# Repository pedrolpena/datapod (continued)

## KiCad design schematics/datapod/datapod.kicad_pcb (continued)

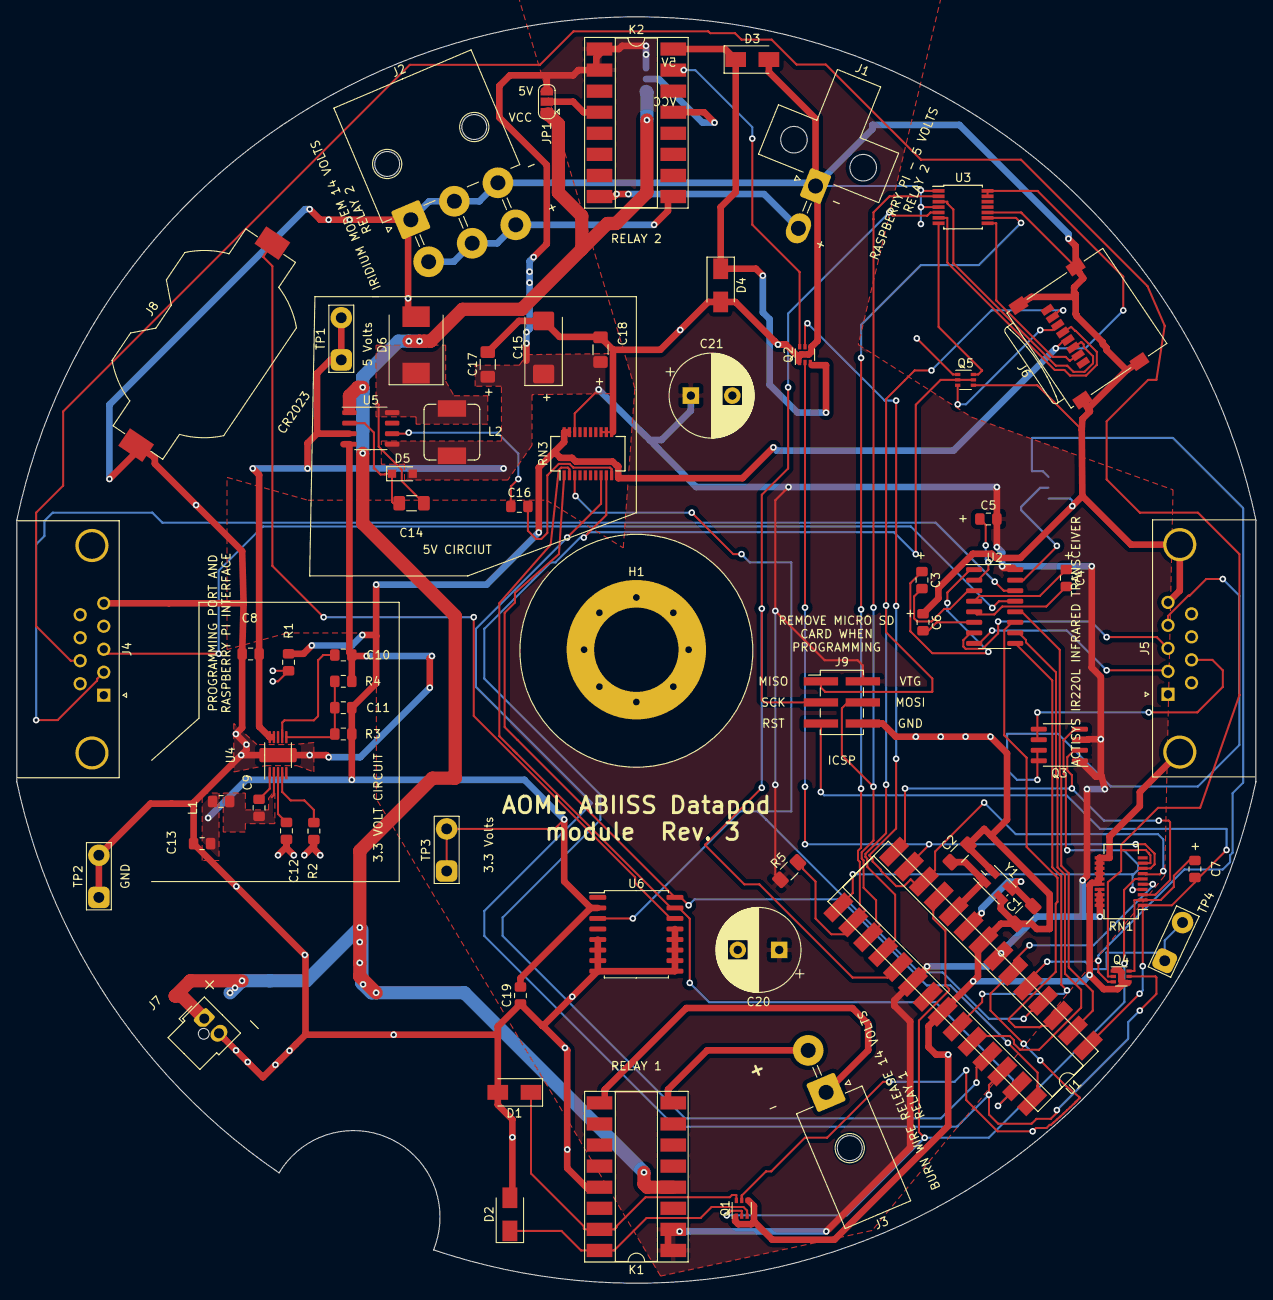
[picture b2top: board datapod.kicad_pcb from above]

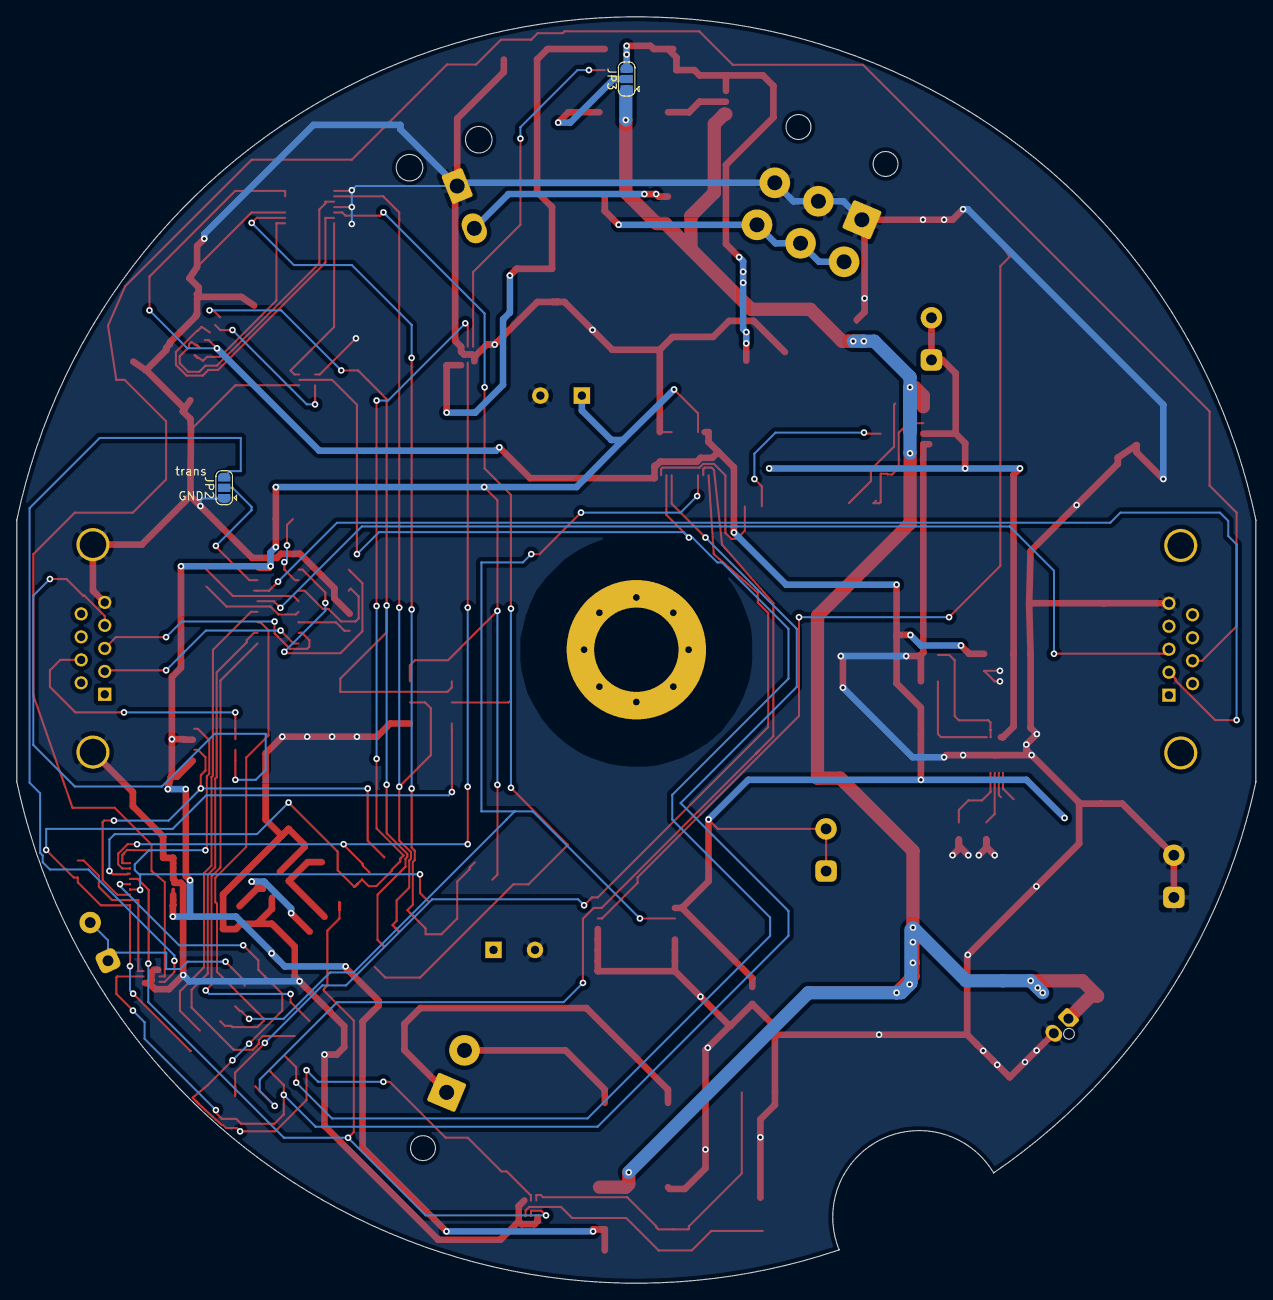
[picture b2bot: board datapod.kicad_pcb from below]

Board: 2 copper layers, 149.3 x 152.6 mm, 67 parts (2 on the bottom side), 69 nets.

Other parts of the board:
JP3: Jumper_3_Open; SolderJumper-3_P1.3mm_Open_RoundedPad1.0x1.5mm

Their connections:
+5V: JP3.3; also elsewhere on the board

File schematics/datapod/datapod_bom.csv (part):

Reference, Value, Vendor, Part#, Footprint, Datasheet,, extra, part#,, Datasheet2, Value2, Part#-2, Field4, Field5, Field6, Field7, Field8
Y1,16Mhz,Digikey,SER3686DKR-ND,Oscillator:Oscillator_SMD_EuroQuartz_XO32-4Pin_3.2x2.5mm_HandSoldering,https://support.epson.biz/td/api/doc_check.php?dl=brief_FA-2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,,https://www.digikey.com/product-detail/en/epson/FA-238-16.00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,,,,,,,,,,
C1,22pF,Digikey,399-8165-1-ND,Capacitor_SMD:C_1206_3216Metric_Pad1.42x1.75mm_HandSolder,https://api.kemet.com/component-edge/download/datasheet/C120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,,,,,,,,,,,,
RN1,R_Pack 10k Ohms,Digikey,OSOPT-10KACT-ND ,Package_SO:SSOP-20_3.9x8.7mm_P0.635mm,http://www.vishay.com/docs/60002/osop.pdf,,,,,,,,,,,,
C2,22pF,Digikey,399-8165-1-ND,Capacitor_SMD:C_1206_3216Metric_Pad1.42x1.75mm_HandSolder,https://api.kemet.com/component-edge/download/datasheet/C120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,,,,,,,,,,,,
H1,MountingHole,,N/A,datapod:MountingHole_0.4_inches_Pad_Via,~,,,,,,,,,,,,
U1,ATmega328P-PU,  ,N/A,Package_DIP:DIP-28_W7.62mm_SMDSocket_SmallPads,http://ww1.microchip.com/downloads/en/DeviceDoc/ATmega328_P%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,,,,,https://www.digikey.com/products/en?mpart=110-47-328-41-105000&v=54,110-47-328-41-105000 ,,,,,,
J9,Conn_02x03_Odd_Even,Digikey,1175-1864-ND,Connector_PinHeader_2.54mm:PinHeader_2x03_P2.54mm_Vertical_SMD,http://www.cnctech.us/pdfs/3020-XX-0300-00-TR.pdf,,,,,,,,,,,,
TP2,TestPoint_2Pole,,N/A,TestPoint:TestPoint_2Pads_Pitch5.08mm_Drill1.3mm,~,,,,,,,,,,,,
TP4,TestPoint_2Pole,,N/A,TestPoint:TestPoint_2Pads_Pitch5.08mm_Drill1.3mm,~,,,,,,,,,,,,
Q1,FDG1024NZ,Digikey,FDG1024NZFSCT-ND,Package_TO_SOT_SMD:SOT-363_SC-70-6,http://www.fairchildsemi.com/ds/FD/FDG1024NZ.pdf,,,,,,,,,,,,
D1,B220A-13-F ,Digikey,B220A-FDIDKR-ND,Diode_SMD:D_SMA,http://www.jameco.com/Jameco/Products/ProdDS/1538777.pdf,,,,,,,,,,,,
D2,B220A-13-F ,Digikey,B220A-FDIDKR-ND,Diode_SMD:D_SMA,http://www.jameco.com/Jameco/Products/ProdDS/1538777.pdf,,,,,,,,,,,,
Q2,FDG1024NZ,Digikey,FDG1024NZFSCT-ND,Package_TO_SOT_SMD:SOT-363_SC-70-6,http://www.fairchildsemi.com/ds/FD/FDG1024NZ.pdf,,,,,,,,,,,,
D3,B220A-13-F ,Digikey,B220A-FDIDKR-ND,Diode_SMD:D_SMA,http://www.jameco.com/Jameco/Products/ProdDS/1538777.pdf,,,,,,,,,,,,
D4,B220A-13-F ,Digikey,B220A-FDIDKR-ND,Diode_SMD:D_SMA,http://www.jameco.com/Jameco/Products/ProdDS/1538777.pdf,,,,,,,,,,,,
K1,DS2E-SL2-DC5V,Digikey,ED11086-ND,Package_DIP:DIP-16_W7.62mm_SMDSocket_SmallPads,https://www3.panasonic.biz/ac/e_download/control/relay/signa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,,,,,,,255-1066-ND,,,,,
J3,Conn_01x02,Digikey,WM11969-ND,Connector_Molex:Molex_Mega-Fit_76825-0002_2x01_P5.70mm_Horizontal,https://media.digikey.com/pdf/Data%20Sheets/Molex%20PDFs/Meg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,,,,,,,,,,,,
J2,Conn_02x03_Odd_Even,Digikey,WM11971-ND,Connector_Molex:Molex_Mega-Fit_76825-0006_2x03_P5.70mm_Horizontal,https://www.molex.com/pdm_docs/as/AS-76823-100.pdf,,,,,,,,,,,,
J1,Conn_01x02,Digikey,WM3900-ND,Connector_Molex:Molex_Mini-Fit_Jr_5569-02A1_2x01_P4.20mm_Horizontal,https://www.molex.com/pdm_docs/sd/039291028_sd.pdf,,,,,,,,,,,,
K2,DS2E-SL2-DC5V,Digikey,ED11086-ND,Package_DIP:DIP-16_W7.62mm_SMDSocket_SmallPads,https://www3.panasonic.biz/ac/e_download/control/relay/signa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,,,,,,,255-1066-ND,,,,,
JP1,Jumper_3_Open,,N/A,Jumper:SolderJumper-3_P1.3mm_Open_RoundedPad1.0x1.5mm,~,,,,,,,,,,,,
Q4,FDG1024NZ,Digikey,FDG1024NZFSCT-ND,Package_TO_SOT_SMD:SOT-363_SC-70-6,http://www.fairchildsemi.com/ds/FD/FDG1024NZ.pdf,,,,,,,,,,,,
C7,1uF,Digikey, TCJP105M025R0500,Capacitor_SMD:C_0805_2012Metric_Pad1.15x1.40mm_HandSolder,http://datasheets.avx.com/TCJ.pdf,,,,,,,,,,,,
J5,DB9_Male_MountingHoles,Digikey,AE10968-ND,Connector_Dsub:DSUB-9_Male_Horizontal_P2.77x2.84mm_EdgePinOffset7.70mm_Housed_MountingHolesOffset9.12mm,http://www.assmann-wsw.com/fileadmin/datasheets/ASS_4888_CO.pdf,,,,,,,,,,,,
J4,DB9_Female,Digikey,AE10921-ND ,Connector_Dsub:DSUB-9_Female_Horizontal_P2.77x2.84mm_EdgePinOffset7.70mm_Housed_MountingHolesOffset9.12mm,http://www.assmann-wsw.com/fileadmin/datasheets/ASS_4888_CO.pdf,,,,,,,,,,,,
U2,MAX232,Digikey,296-14619-1-ND,Package_SO:SOIC-16_3.9x9.9mm_P1.27mm,http://www.ti.com/lit/ds/symlink/max232.pdf,,,,,,,,,,,,
C3,1uF,Digikey, TCJP105M025R0500,Capacitor_SMD:C_0805_2012Metric_Pad1.15x1.40mm_HandSolder,http://datasheets.avx.com/TCJ.pdf,,,,,,,,,,,,
C5,1uF,Digikey, TCJP105M025R0500,Capacitor_SMD:C_0805_2012Metric_Pad1.15x1.40mm_HandSolder,http://datasheets.avx.com/TCJ.pdf,,,,,,,,,,,,
C6,1uF,Digikey, TCJP105M025R0500,Capacitor_SMD:C_0805_2012Metric_Pad1.15x1.40mm_HandSolder,http://datasheets.avx.com/TCJ.pdf,,,,,,,,,,,,
C4,1uF,Digikey, TCJP105M025R0500,Capacitor_SMD:C_0805_2012Metric_Pad1.15x1.40mm_HandSolder,http://datasheets.avx.com/TCJ.pdf,,,,,,,,,,,,
Q3,IRF7324,Digikey,IRF7324PBFTR-ND,Package_SO:SOIC-8_3.9x4.9mm_P1.27mm,http://www.infineon.com/dgdl/irf7324pbf.pdf?fileId=5546d4625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,,,,,,,,,,,,
JP2,SolderJumper_3_Open,,N/A,Jumper:SolderJumper-3_P1.3mm_Open_RoundedPad1.0x1.5mm,~,,,,,,,,,,,,
U3,74LVC125,Digikey,296-1222-1-ND,Package_SO:TSSOP-14_4.4x5mm_P0.65mm,http://www.ti.com/general/docs/suppproductinfo.tsp?distId=10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,,,,,,,,,,,,
J6,Micro_SD_Card,Digikey,732-3820-1-ND,Connector_Card:microSD_HC_Wuerth_693072010801,http://katalog.we-online.de/em/datasheet/693072010801.pdf,,,,,,,,,,,,
R5,10K,Digikey,749-1125-6-ND,Resistor_SMD:R_1206_3216Metric_Pad1.42x1.75mm_HandSolder,http://www.vishay.com/docs/28796/mcw0406atpro.pdf,,,,,,,,,,,,
Q5,FDG1024NZ,Digikey,FDG1024NZFSCT-ND,Package_TO_SOT_SMD:SOT-363_SC-70-6,http://www.fairchildsemi.com/ds/FD/FDG1024NZ.pdf,,,,,,,,,,,,
R1,"100k, 1%",Digikey,311-100KCRCT-ND,Resistor_SMD:R_0805_2012Metric_Pad1.15x1.40mm_HandSolder,http://www.yageo.com/documents/recent/PYu-RC_Group_51_RoHS_L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,,,,,,,,,,,,
R3,"1M, 1%",Digikey,311-1.00MCRCT-ND,Resistor_SMD:R_0805_2012Metric_Pad1.15x1.40mm_HandSolder,http://www.yageo.com/documents/recent/PYu-RC_Group_51_RoHS_L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,,,,,,,,,,,,
R2,"18.2k, 1%",Digikey,311-18.2KCRCT-ND,Resistor_SMD:R_0805_2012Metric_Pad1.15x1.40mm_HandSolder,http://www.yageo.com/documents/recent/PYu-RC_Group_51_RoHS_L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,,,,,,,,,,,,
C8,4.7uF,Digikey,490-12753-1-ND,Capacitor_SMD:C_0805_2012Metric_Pad1.15x1.40mm_HandSolder,https://search.murata.co.jp/Ceramy/image/img/A01X/G101/ENG/G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,,,,,,,,,,,,
C9,.1uF,Digikey,478-3351-1-ND,Capacitor_SMD:C_0805_2012Metric_Pad1.15x1.40mm_HandSolder,http://datasheets.avx.com/X7RDielectric.pdf,,,,,,,,,,,,
C10,10nF,Digikey,311-1136-1-ND,Capacitor_SMD:C_0805_2012Metric_Pad1.15x1.40mm_HandSolder,http://www.yageo.com/documents/recent/UPY-GPHC_X7R_6.3V-to-5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,,,,,,,,,,,,
C11,10pF,Digikey,399-7062-1-ND,Capacitor_SMD:C_0805_2012Metric_Pad1.15x1.40mm_HandSolder,https://api.kemet.com/component-edge/download/datasheet/C080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,,,,,,,,,,,,
C13,22uF,Digikey,1276-6780-1-ND,Capacitor_SMD:C_0805_2012Metric_Pad1.15x1.40mm_HandSolder,http://www.samsungsem.com/kr/support/product-search/mlcc/CL2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,,,,,,,,,,,,
C12,1uF,Digikey,311-1365-1-ND,Capacitor_SMD:C_0805_2012Metric_Pad1.15x1.40mm_HandSolder,http://www.yageo.com/documents/recent/UPY-GPHC_X7R_6.3V-to-5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,,,,,,,,,,,,
L1,2.2uH,Digikey,587-2771-1-ND,Inductor_SMD:L_0805_2012Metric_Pad1.15x1.40mm_HandSolder,https://ds.yuden.co.jp/TYCOMPAS/ut/detail?pn=CKP2012N2R2M-T%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,,,,,,,,,,,,
R4,"309k, 1%",Digikey,311-309KCRCT-ND,Resistor_SMD:R_0805_2012Metric_Pad1.15x1.40mm_HandSolder,http://www.yageo.com/documents/recent/PYu-RC_Group_51_RoHS_L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,,,,,,,,,,,,
U4,LT8609EMSETRPBF,,LT8609EMSE#TRPBFCT-ND,Package_SO:MSOP-10-1EP_3x3mm_P0.5mm_EP1.73x1.98mm,Linear Technology/Analog,,,,,,,,MSOP-10 Linear Technology,"LT8609/LT8609A/LT8609B - 42V, 2A/3A Peak Synchronous Step-Down Regulator with 2.5μA Quiescent Current",LT8609EMSE#TRPBFCT-ND,LT8609EMSE#TRPBF,https://www.digikey.com/product-detail/en/linear-technology-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
TP3,TestPoint_2Pole,,N/A,TestPoint:TestPoint_2Pads_Pitch5.08mm_Drill1.3mm,~,,,,,,,,,,,,
C15,100uF,Digikey,718-1890-1-ND,Capacitor_Tantalum_SMD:CP_EIA-7343-31_Kemet-D_Pad2.25x2.55mm_HandSolder,http://www.vishay.com/docs/40002/293d.pdf,,,,,,,,,,,,
C16,5000pF,Digikey,478-10560-1-ND,Capacitor_SMD:C_0805_2012Metric_Pad1.15x1.40mm_HandSolder,http://datasheets.avx.com/X7RDielectric.pdf,,,,,,,,,,,,
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
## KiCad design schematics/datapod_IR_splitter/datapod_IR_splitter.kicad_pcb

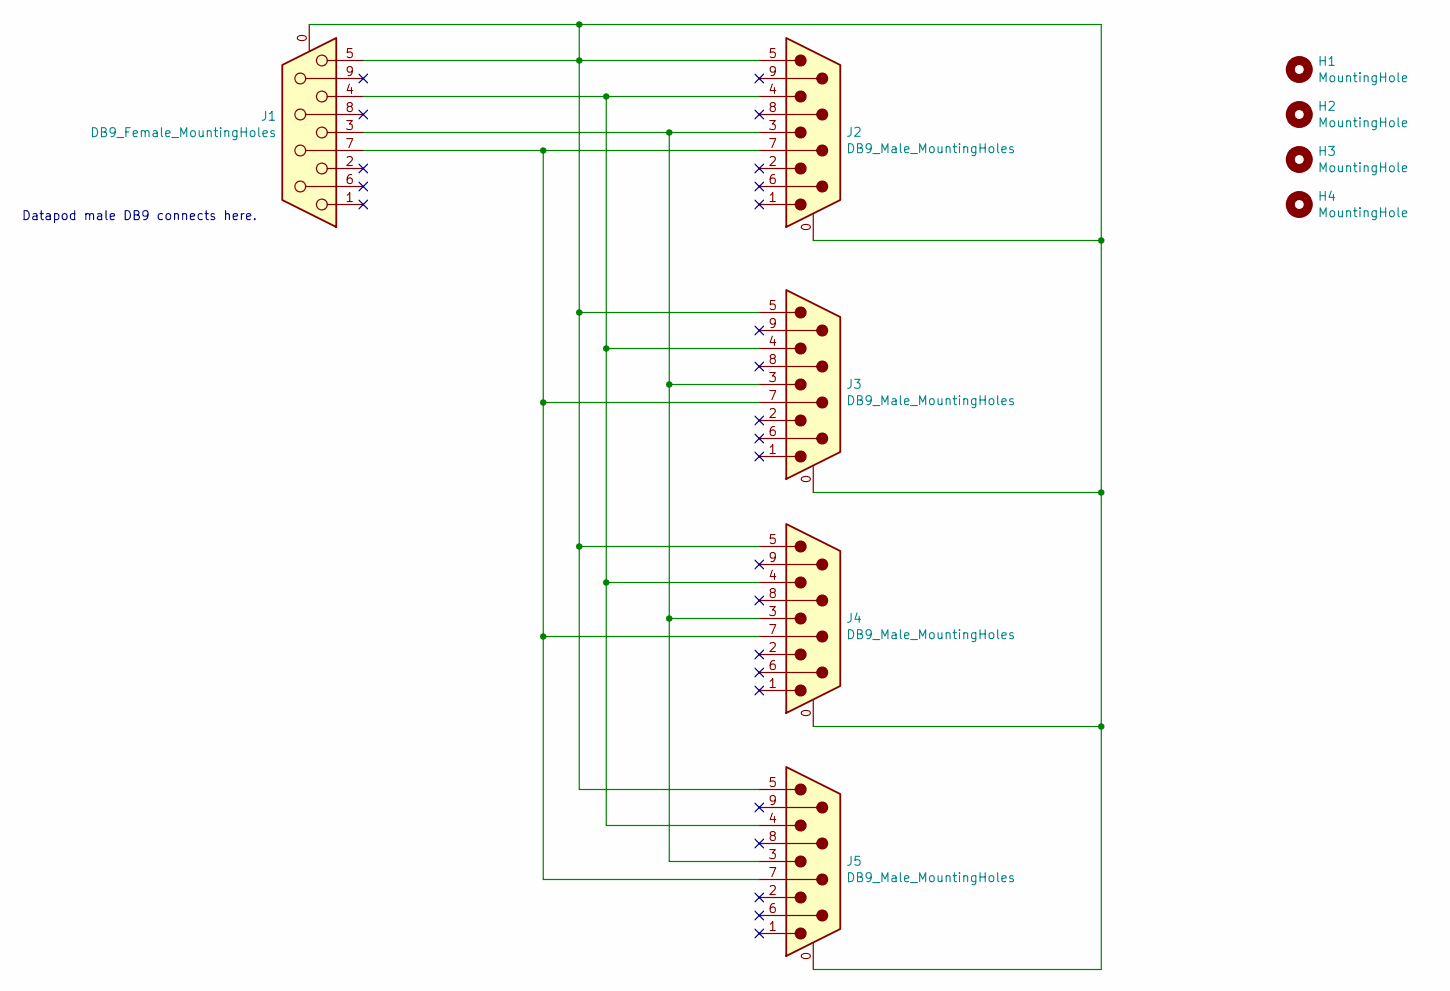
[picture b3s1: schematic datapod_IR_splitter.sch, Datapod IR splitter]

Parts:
H1, H2, H3, H4: MountingHole; MountingHole_4.5mm_Pad
J1: DB9_Female_MountingHoles; DSUB-9_Female_Horizontal_P2.77x2.84mm_EdgePinOffset9.90mm_H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; Part# AE10921-ND
J2, J3, J4, J5: DB9_Male_MountingHoles; DSUB-9_Male_Vertical_P2.77x2.84mm_MountingHoles; Part# 609-5184-ND

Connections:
unnamed: J1.0 (PAD), J1.5, J2.0 (PAD), J2.5, J3.0 (PAD), J3.5, J4.0 (PAD), J4.5, J5.0 (PAD), J5.5
unnamed: J1.3, J2.3, J3.3, J4.3, J5.3
unnamed: J1.4, J2.4, J3.4, J4.4, J5.4
unnamed: J1.7, J2.7, J3.7, J4.7, J5.7

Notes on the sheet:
Datapod male DB9 connects here.

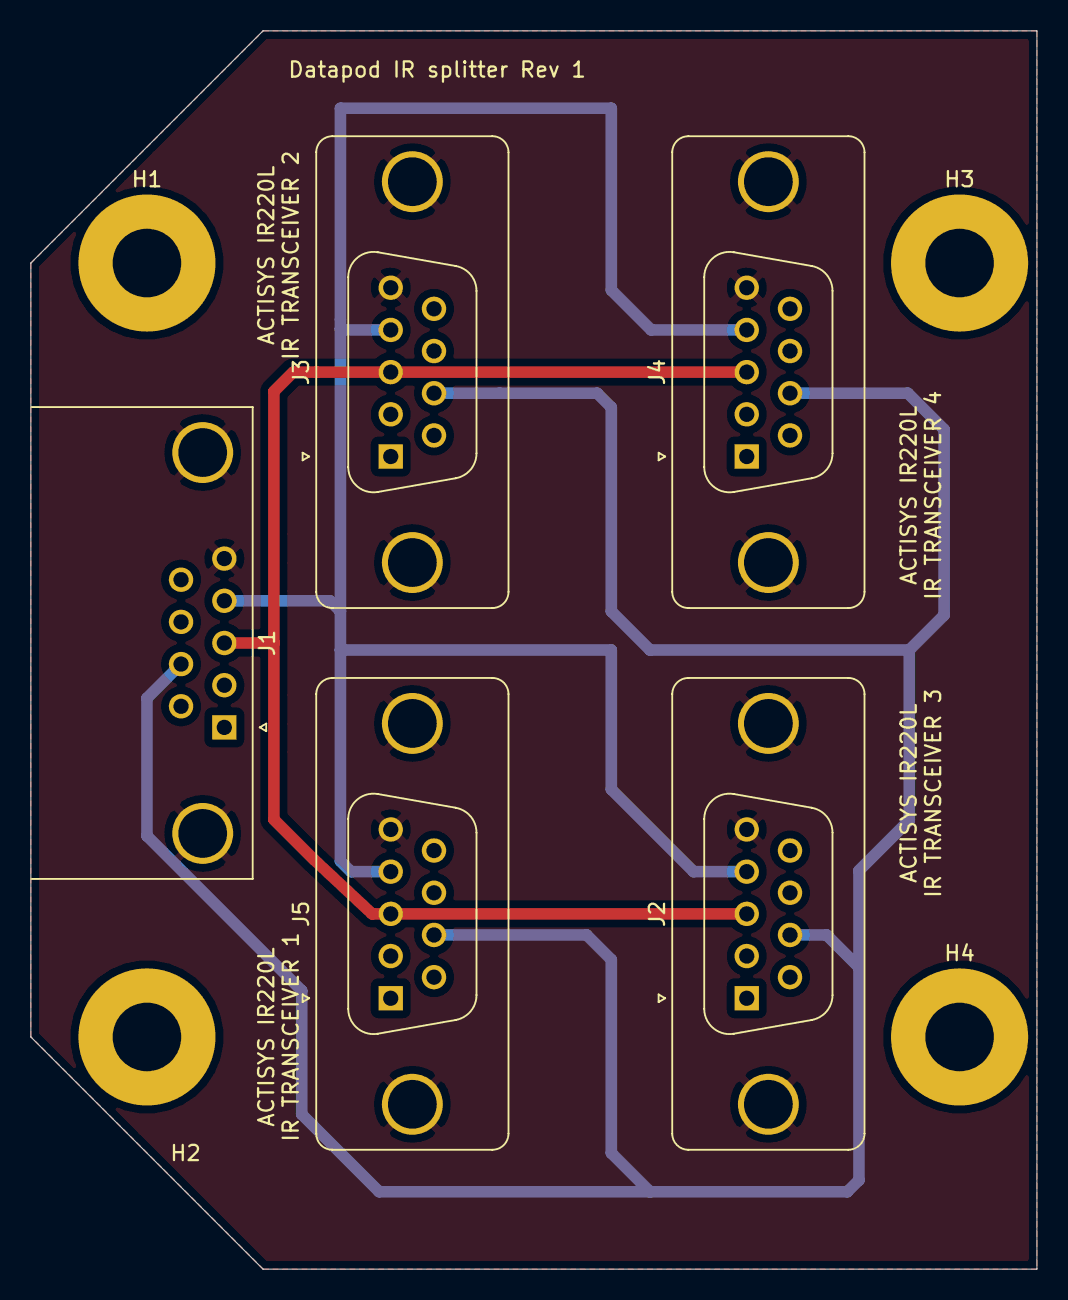
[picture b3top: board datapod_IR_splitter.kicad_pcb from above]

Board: 2 copper layers, 66.0 x 81.3 mm, 9 parts (0 on the bottom side), 4 nets.

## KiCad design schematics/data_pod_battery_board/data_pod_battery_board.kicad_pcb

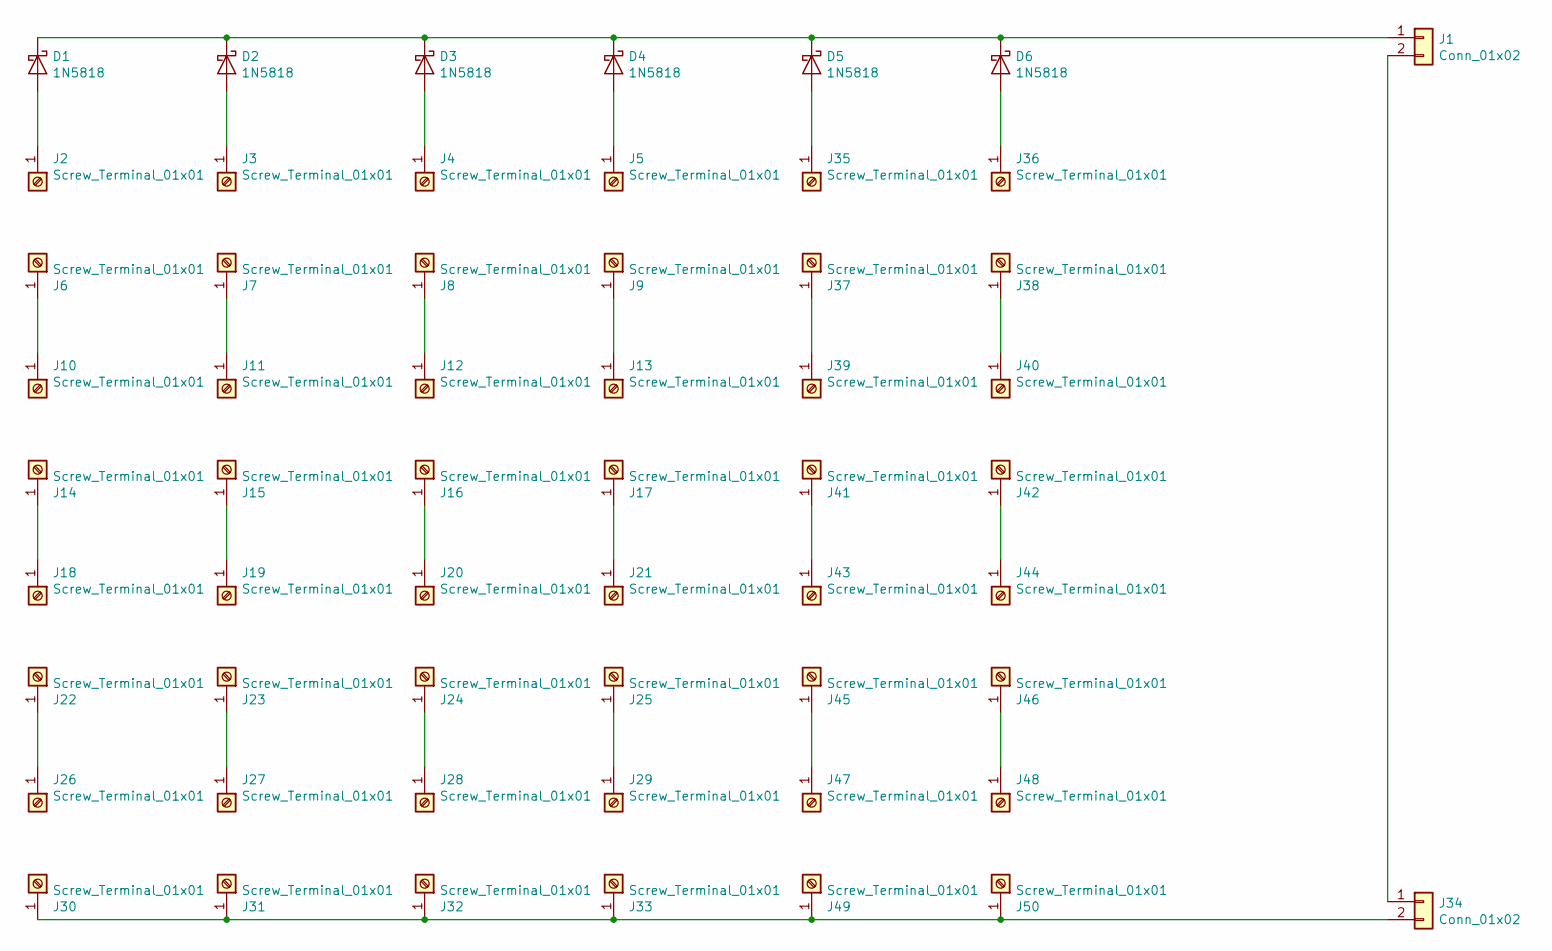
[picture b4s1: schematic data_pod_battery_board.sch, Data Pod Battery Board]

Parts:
D1, D2, D3, D4, D5, D6: 1N5818; D_DO-41_SOD81_P10.16mm_Horizontal; Part# 1N5818-TPCT-ND
J1, J34: Conn_01x02; Molex_Nano-Fit_105309-xx02_1x02_P2.50mm_Vertical; Part# WM15036-ND
J2, J3, J4, J5, J6, J7, J8, J9, J10, J11, J12, J13, J14, J15, J16, J17, J18, J19, J20, J21, J22, J23, J24, J25, J26, J27, J28, J29, J30, J31, J32, J33, J35, J36, J37, J38, J39, J40, J41, J42, J43, J44, J45, J46, J47, J48, J49, J50: Screw_Terminal_01x01; screw_terminal_7.0mmx5.0mm; Part# 36-7691-ND

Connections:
unnamed: D1.1 (K), D2.1 (K), D3.1 (K), D4.1 (K), D5.1 (K), D6.1 (K), J1.1
unnamed: D1.2 (A), J2.1
unnamed: D2.2 (A), J3.1
unnamed: D3.2 (A), J4.1
unnamed: D4.2 (A), J5.1
unnamed: D5.2 (A), J35.1
unnamed: D6.2 (A), J36.1
unnamed: J1.2, J34.1
unnamed: J6.1, J10.1
unnamed: J7.1, J11.1
unnamed: J8.1, J12.1
unnamed: J9.1, J13.1
unnamed: J14.1, J18.1
unnamed: J15.1, J19.1
unnamed: J16.1, J20.1
unnamed: J17.1, J21.1
unnamed: J22.1, J26.1
unnamed: J23.1, J27.1
unnamed: J24.1, J28.1
unnamed: J25.1, J29.1
unnamed: J30.1, J31.1, J32.1, J33.1, J34.2, J49.1, J50.1
unnamed: J37.1, J39.1
unnamed: J38.1, J40.1
unnamed: J41.1, J43.1
unnamed: J42.1, J44.1
unnamed: J45.1, J47.1
unnamed: J46.1, J48.1

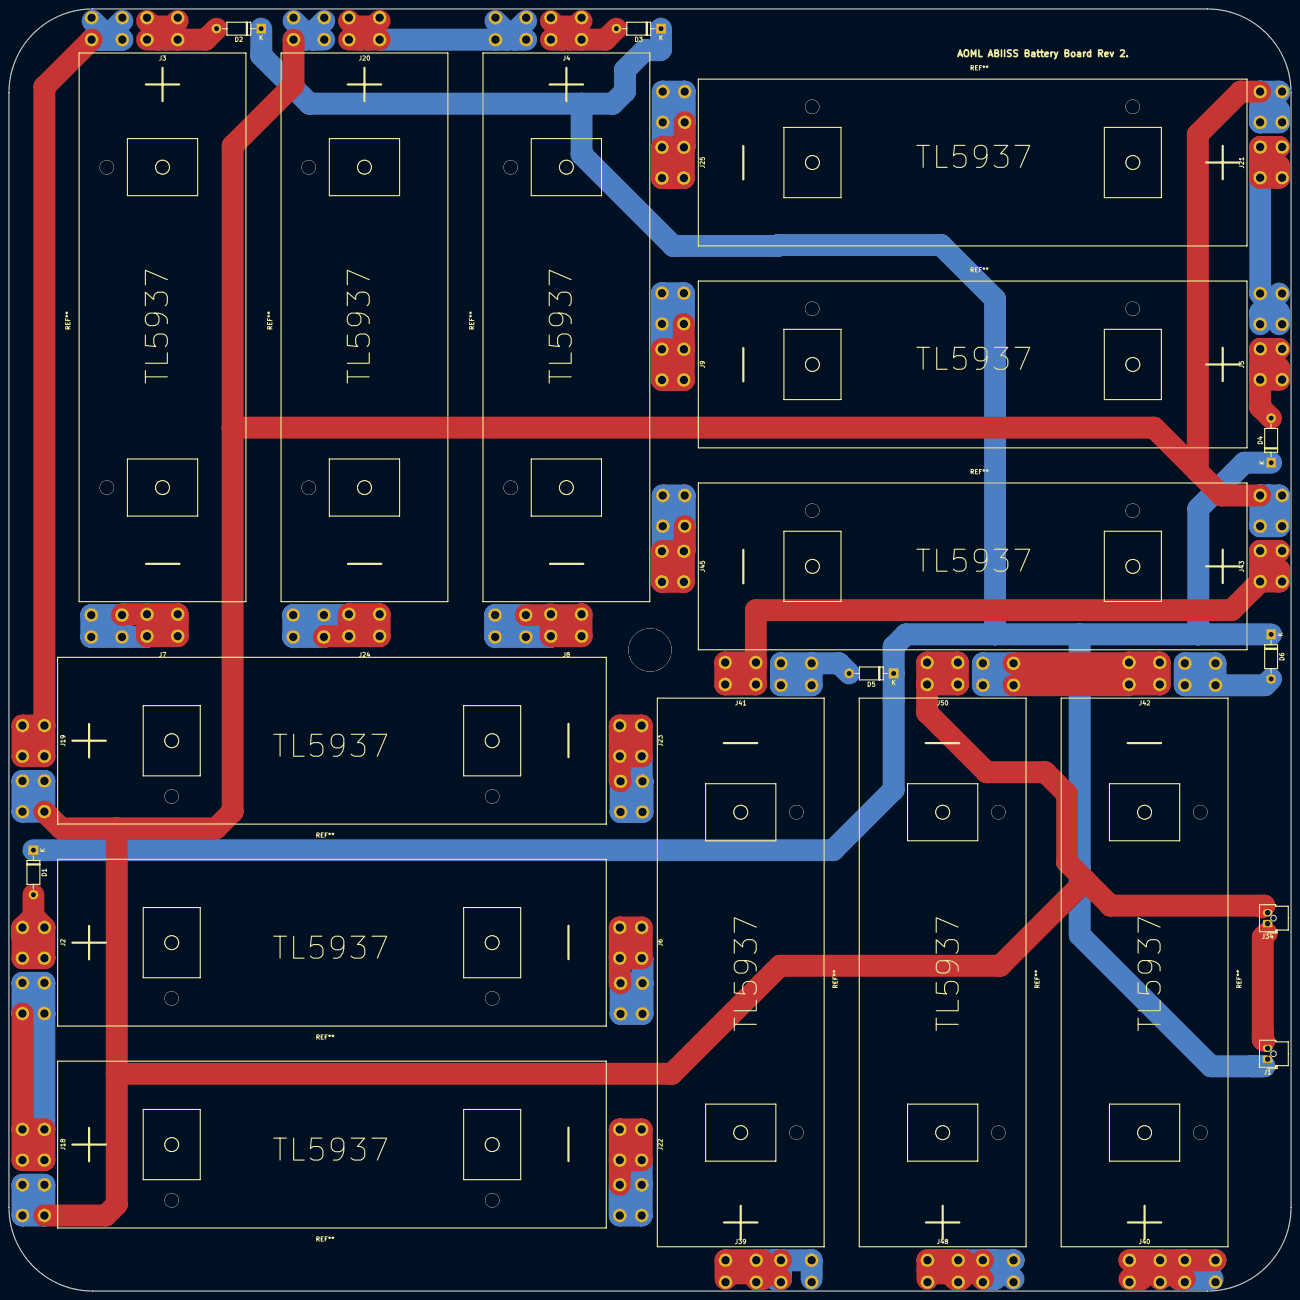
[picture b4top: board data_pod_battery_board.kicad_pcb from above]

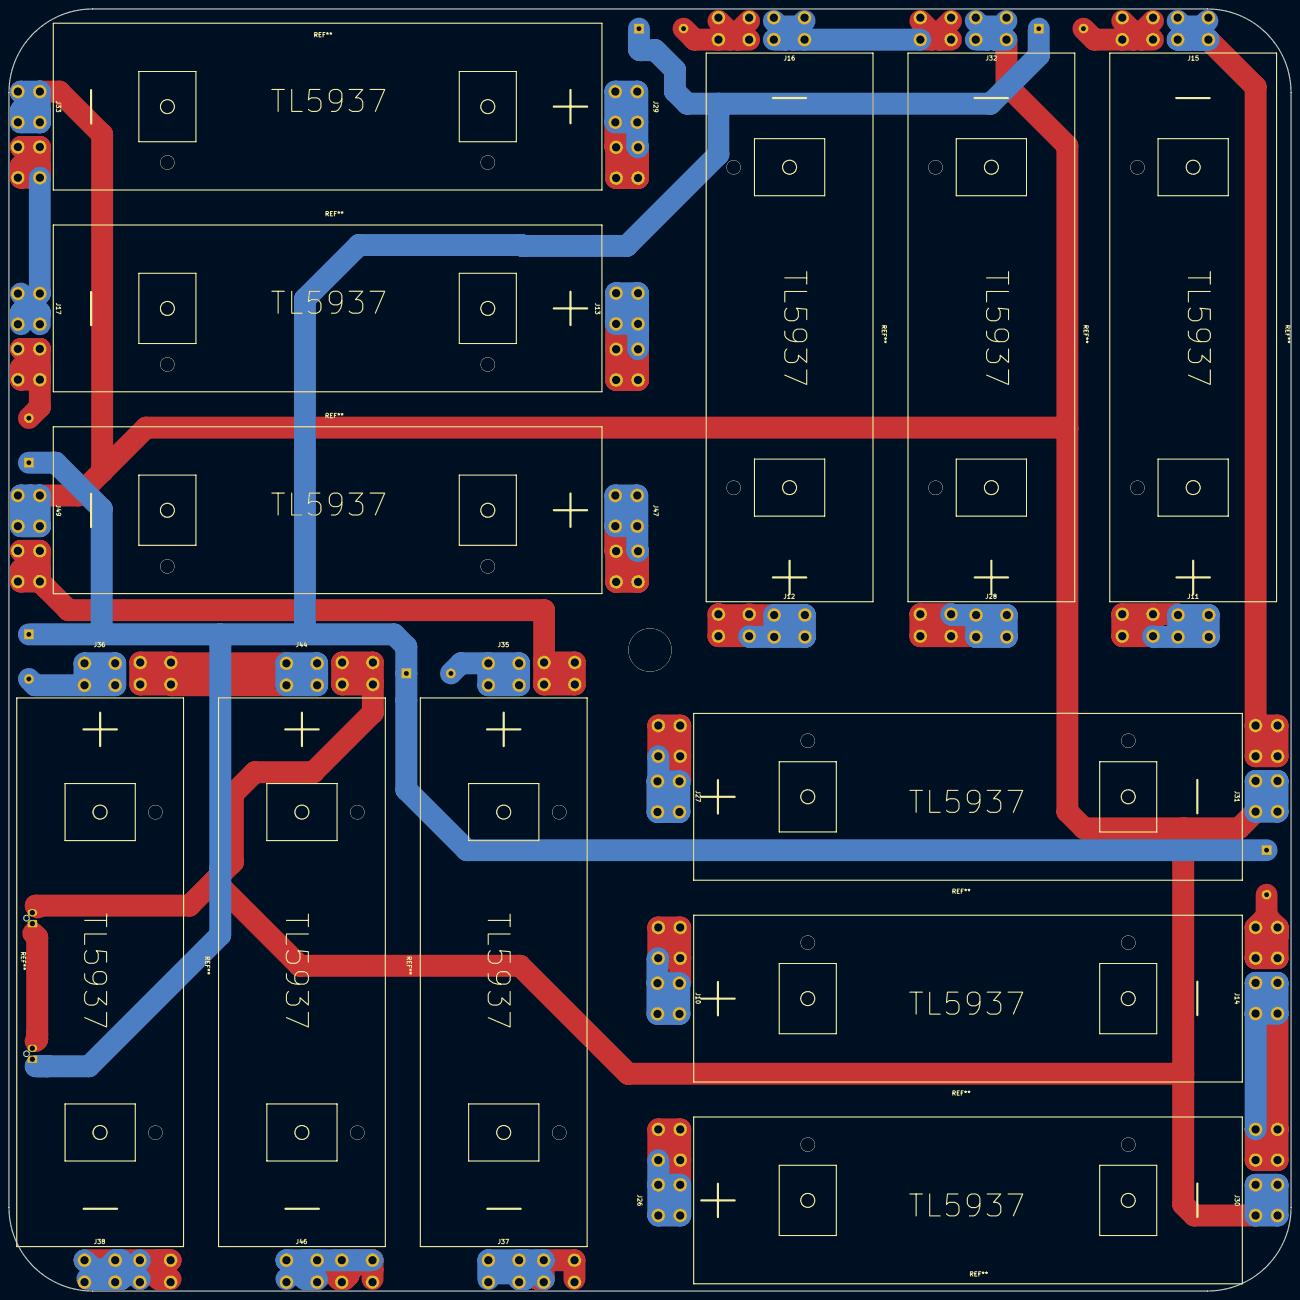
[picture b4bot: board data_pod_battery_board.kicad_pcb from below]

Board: 2 copper layers, 292.1 x 292.1 mm, 56 parts (24 on the bottom side), 27 nets.

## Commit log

2019-11-04 Added schematic for datapod
2019-11-04 modified schematic
2019-11-05 added more connectors and started drawing the PCB
2019-11-05 made 1st pcb
2019-11-06 finished routing now removing warnings
2019-11-06 added final routed PCB, gerbers and BOM
2019-11-06 refreshed gerber/drill file and added 3d step files
2019-11-07 added some more 3d models
2019-11-07 added 3d renderings
2019-11-08 added initial schematic for the battery board
2019-11-08 created footprint for terminal
2019-11-08 improved pcb outline
2019-11-12 improved layout a little
2019-11-13 made some more changes to pcb
2019-11-15 added more changes
2019-11-18 finished battery baord pcb
2019-11-18 added gerbers
2019-11-20 final rev1
2019-11-25 replaced rn2 with 4 resistors and moved sd card closer to mcu
2019-12-01 added 3d models that somehow were lost.
2019-12-12 increased the hole diameter for the terminal holes to 1.875 from 1.6
2019-12-12 added gerber files for battery board
2019-12-12 added text the pcb rev2
2020-01-09 restored lost changes... moving sd card reader and replacing rn2 with actual resistors
2020-01-12 fixed bad gnd trace on 3.3v circuit and added comments to the silkscreen
2020-01-13 added a jumper to select between 5v and 14v for the raspberry pi
2020-01-14 added max234 library
2020-01-16 added rtc stuff , rotated db9s , added on/off transistors for max chip and sdcard
2020-01-17 added a fabrication file, updated gerbers to include fab masks, and updated R5 part number
2020-01-18 added datapod IR splitter board
2020-01-20 increased distance between db9 connectors and added notes to transfer file with rx on the terminal
2020-01-27 updated code to reflect pcb change and added interrupt to code
2020-01-30 added a reference marker to C7 to know its orientation when installing
2020-02-04 rev 3 , moved db9 connectors out and added ajumper to change output to 14.4v
2020-02-05 added two capacitors
2020-02-13 added a3la converter board
2020-03-23 updated datapod stuff
